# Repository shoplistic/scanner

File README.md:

# Barcode Scanner

### Links
[Headless Setup](https://desertbot.io/blog/headless-pi-zero-w-wifi-setup-windows)  
[Original Source](https://www.pyimagesearch.com/2018/05/21/an-opencv-barcode-and-qr-code-scanner-with-zbar/)

### TODO:
* [x] Install script
* [ ] Diagram / Schematic
* [x] pwm?

### RPi Pinout
|  pin  |  bcm  | usecase         |
| :---: | :---: | :---            |
|  11   |  17   | RED LED         |
|  12   |  18   | LIGHTNING PWM   |
|  13   |  27   | GREEN LED       |
|  15   |  22   | BLUE LED        |
|  16   |  23   | SENSOR          |

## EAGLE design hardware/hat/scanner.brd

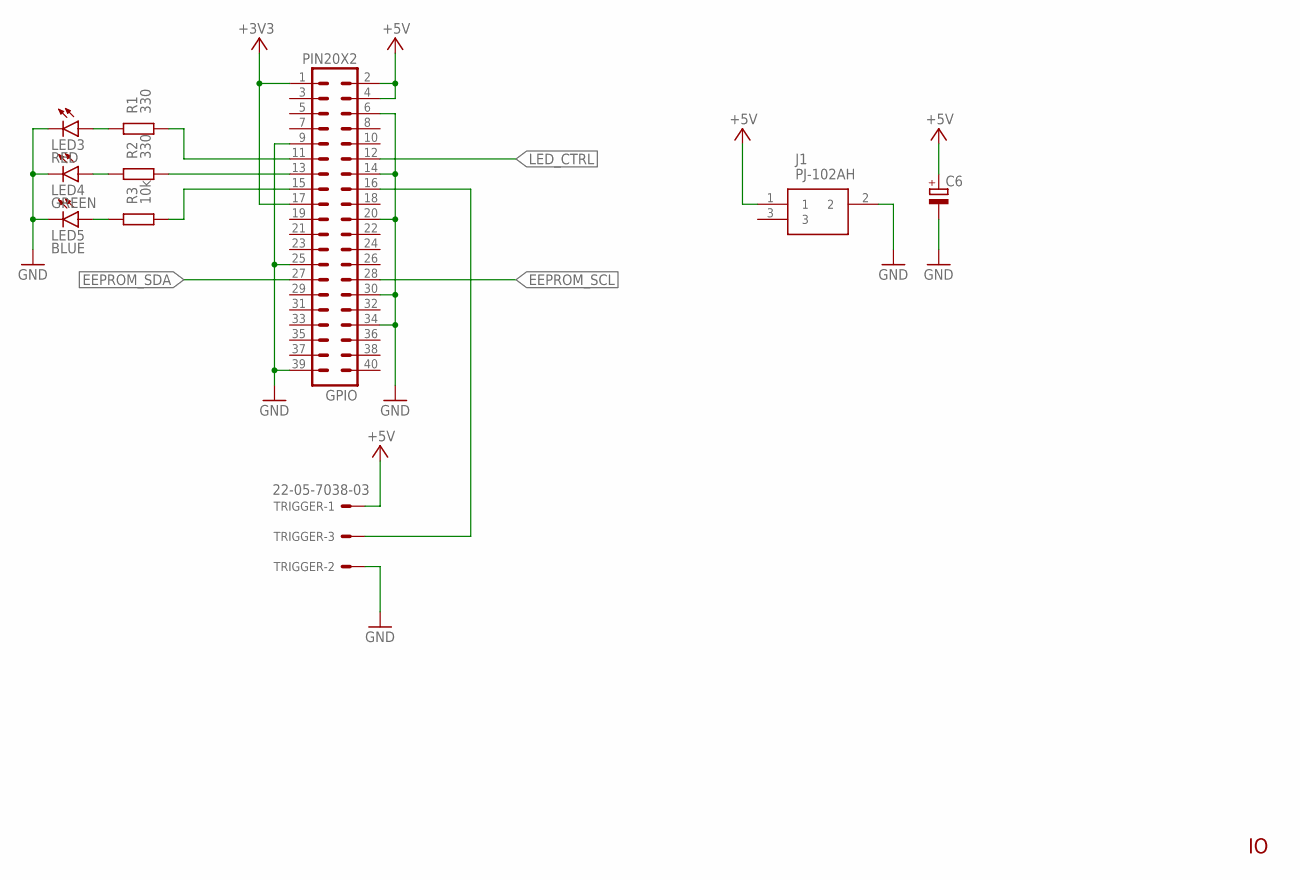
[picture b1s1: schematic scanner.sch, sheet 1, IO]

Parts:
C6: CPOL-EUCT6032; CT6032
GPIO: PIN20X2; PIN_20X2
J1: PJ-102AH
LED3: RED; CHIP-LED0805
LED4: GREEN; CHIP-LED0805
LED5: BLUE; CHIP-LED0805
R1, R2: 330; M0805; TOLERANCE 5%
R3: 10k; M0805; TOLERANCE 5%
TRIGGER: 22-05-7038-03; 7395-03

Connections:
+3V3: GPIO.1, GPIO.17; also elsewhere on the board
+5V: C6.+, GPIO.2, GPIO.4, J1.1, TRIGGER.1; also elsewhere on the board
EEPROM_SCL: GPIO.28; also elsewhere on the board
EEPROM_SDA: GPIO.27; also elsewhere on the board
GND: C6.-, GPIO.6, GPIO.9, GPIO.14, GPIO.20, GPIO.25, GPIO.30, GPIO.34, GPIO.39, J1.2, LED3.C, LED4.C, LED5.C, TRIGGER.2; also elsewhere on the board
LED3: GPIO.11, R1.1
LED4: GPIO.13, R2.1
LED5: GPIO.15, R3.1
LED_CTRL: GPIO.12; also elsewhere on the board
unnamed: LED3.A, R1.2
unnamed: LED4.A, R2.2
unnamed: LED5.A, R3.2
TRIGGER: GPIO.16, TRIGGER.3

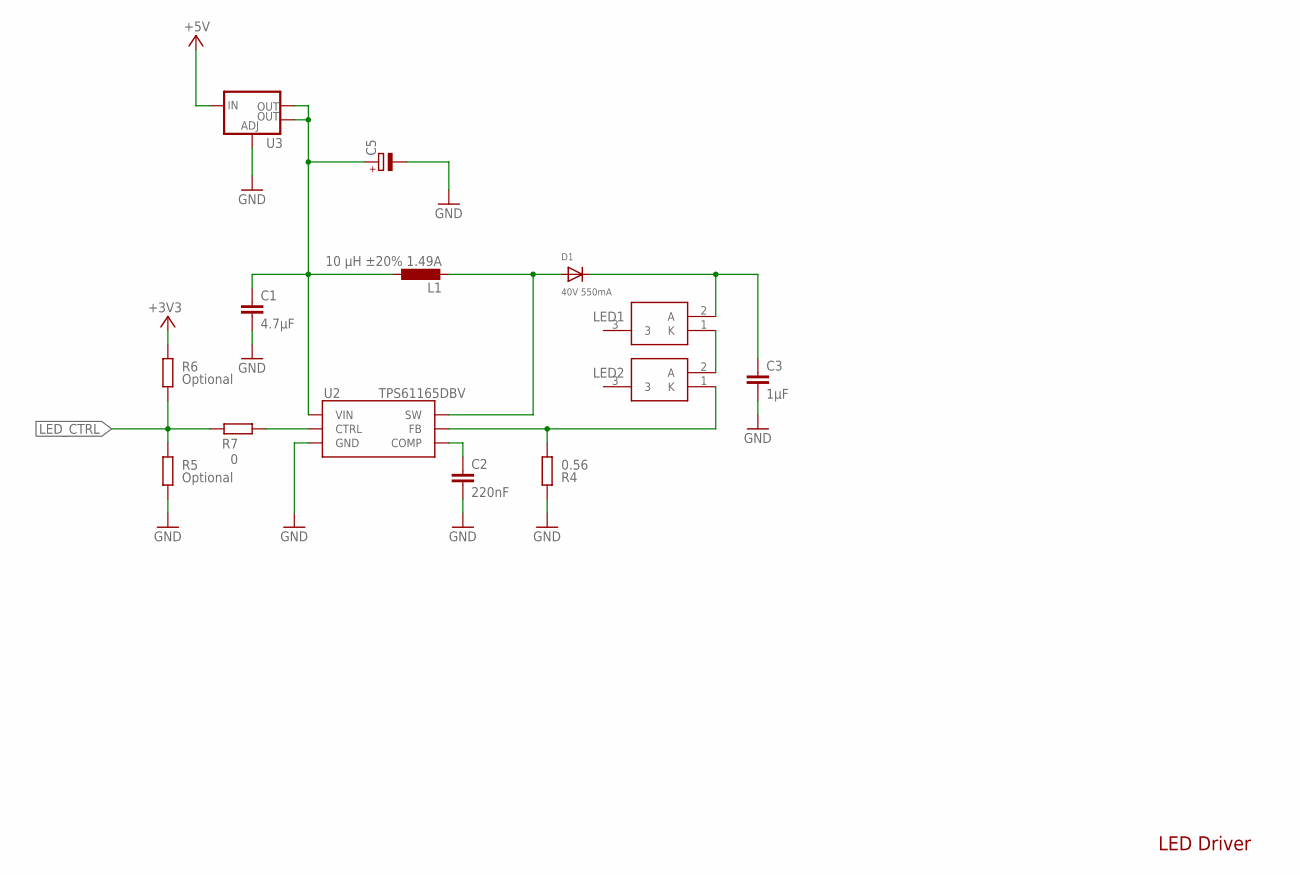
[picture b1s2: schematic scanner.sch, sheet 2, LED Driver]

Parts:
C1: 4.7μF; C0805K
C2: 220nF; C0805K
C3: 1μF; C0805K
C5: CPOL-EUCT6032; CT6032
D1: 40V 550mA; SOD-123
L1: 10 μH ±20% 1.49A; D53LC
LED1, LED2: LW_W5SM-JYKY-JKQL-1; LWW5SMJYKYJKQL1
R4: 0.56; M0805; TOLERANCE 5%
R5, R6: Optional; M0805; TOLERANCE 5%
R7: 0; M0805; TOLERANCE 5%
U2: TPS61165DBV; SOT-23-6
U3: V_REG_LM1117SOT223; SOT223

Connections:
+3V3: R6.2; also elsewhere on the board
+5V: U3.3 (IN); also elsewhere on the board
GND: C1.2, C2.2, C3.2, C5.-, R4.2, R5.1, U2.4 (GND), U3.1 (ADJ); also elsewhere on the board
LED_COMP: C2.1, U2.5 (COMP)
LED_CTRL: R5.2, R6.1, R7.2; also elsewhere on the board
LED_CTRL1: R7.1, U2.2 (CTRL)
LED_FB: LED2.1 (K), R4.1, U2.6 (FB)
LED_SW: D1.A, L1.2, U2.3 (SW)
unnamed: C3.1, D1.C, LED1.2 (A)
unnamed: LED1.1 (K), LED2.2 (A)
VCC: C1.1, C5.+, L1.1, U2.1 (VIN), U3.2 (OUT), U3.4 (OUT)

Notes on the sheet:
LED Driver

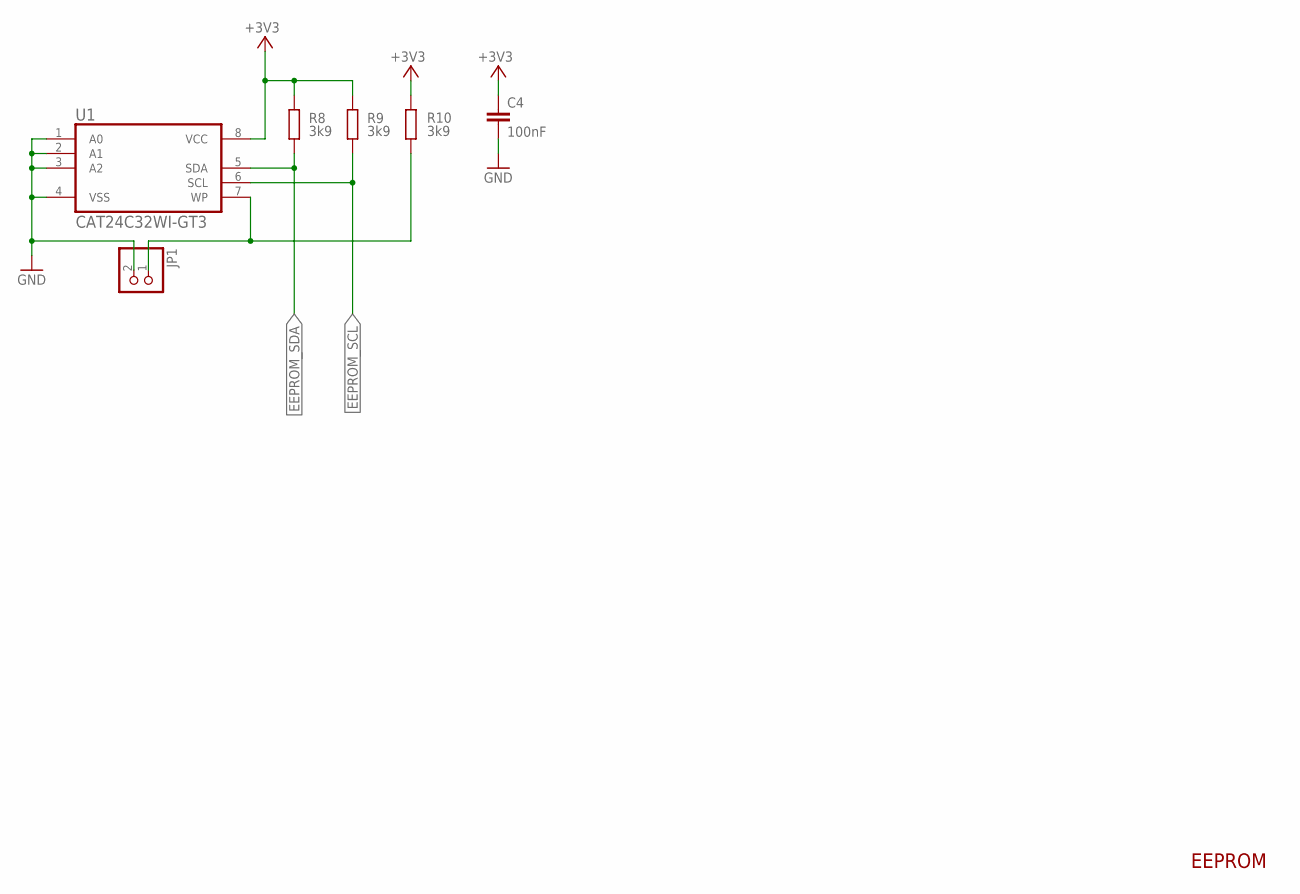
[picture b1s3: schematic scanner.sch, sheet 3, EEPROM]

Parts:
C4: 100nF; C0805K
JP1: PINHD-1X2; 1X02
R8, R9, R10: 3k9; M0805; TOLERANCE 5%
U1: CAT24C32WI-GT3; SOIC127P600X175-8N

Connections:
+3V3: C4.1, R8.2, R9.2, R10.1, U1.8 (VCC); also elsewhere on the board
EEPROM_SCL: R9.1, U1.6 (SCL); also elsewhere on the board
EEPROM_SDA: R8.1, U1.5 (SDA); also elsewhere on the board
EEPROM_WP: JP1.1, R10.2, U1.7 (WP)
GND: C4.2, JP1.2, U1.1 (A0), U1.2 (A1), U1.3 (A2), U1.4 (VSS); also elsewhere on the board

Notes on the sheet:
EEPROM

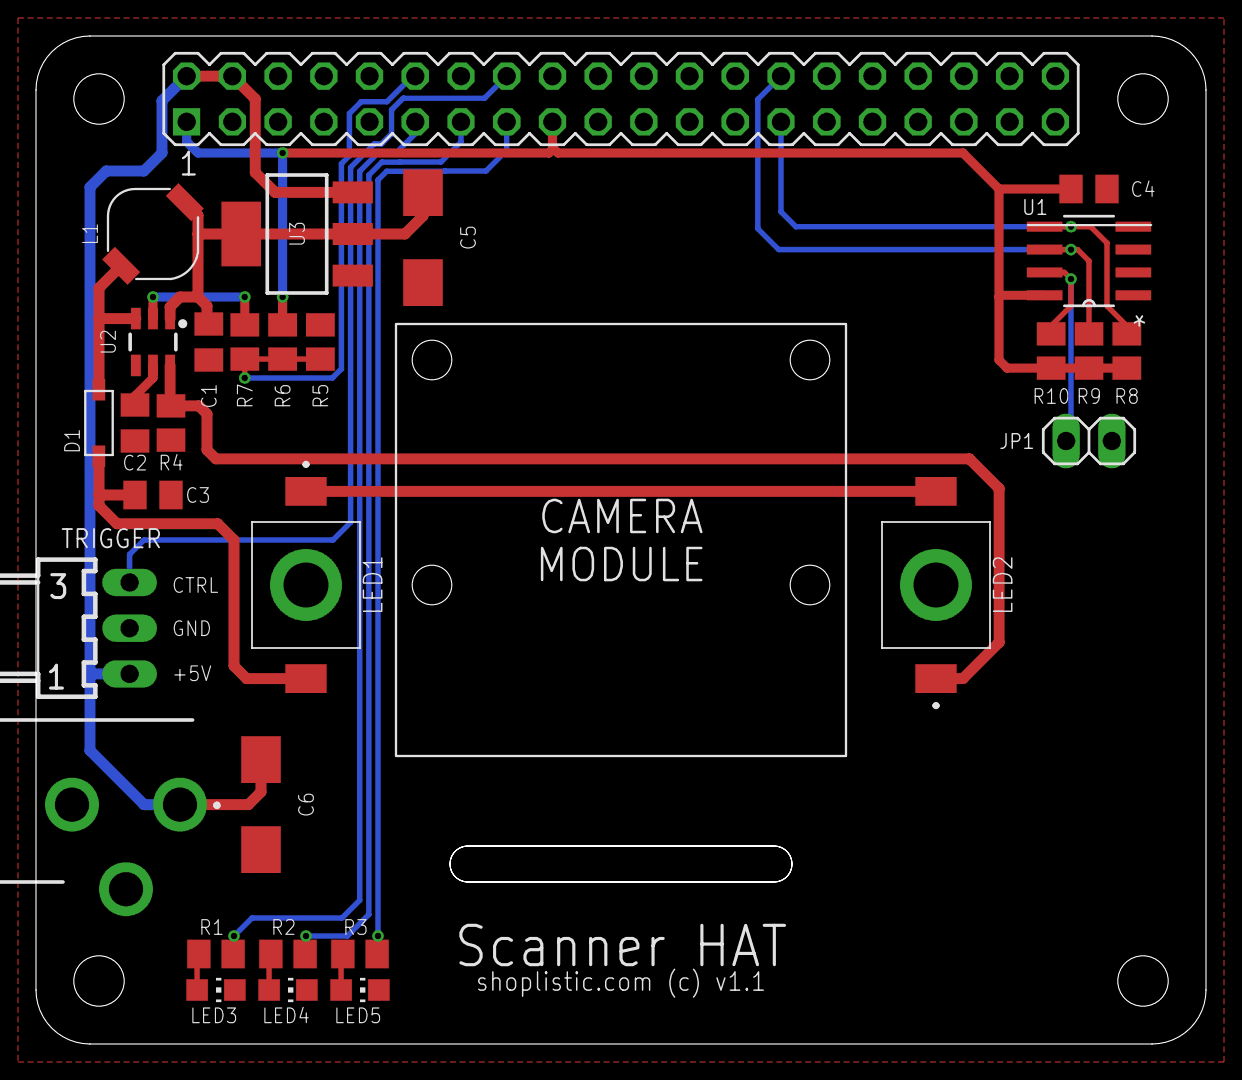
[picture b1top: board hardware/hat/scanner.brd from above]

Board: 2 copper layers, 65.0 x 56.0 mm, 30 parts (0 on the bottom side), 21 nets.

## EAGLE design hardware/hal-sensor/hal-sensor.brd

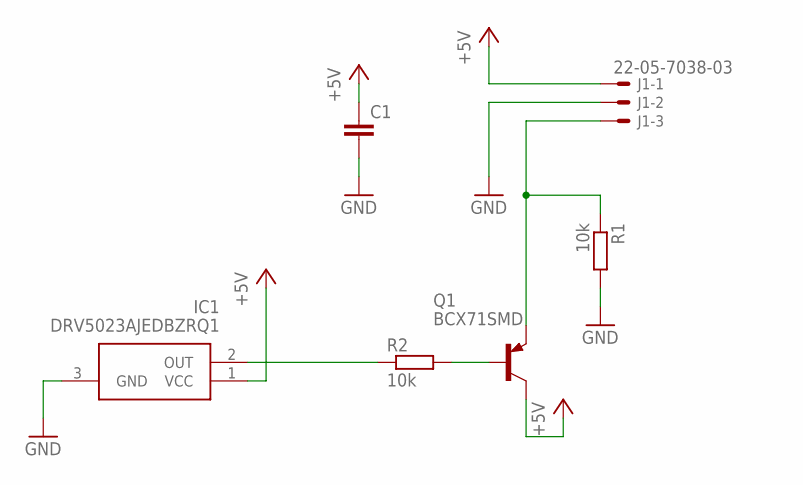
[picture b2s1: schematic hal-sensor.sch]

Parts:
C1: C-EUC0805; C0805
IC1: DRV5023AJEDBZRQ1; SOT95P237X112-3N
J1: 22-05-7038-03; 7395-03
Q1: BCX71SMD; SOT23
R1, R2: 10k; R0805

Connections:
+5V: C1.1, IC1.1 (VCC), J1.1, Q1.3 (C)
CTRL: J1.3, Q1.2 (E), R1.1
GND: C1.2, IC1.3 (GND), J1.2, R1.2
unnamed: IC1.2 (OUT), R2.1
unnamed: Q1.1 (B), R2.2

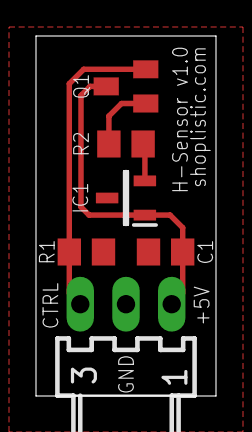
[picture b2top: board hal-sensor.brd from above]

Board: 2 copper layers, 10.0 x 20.0 mm, 6 parts (0 on the bottom side), 5 nets.

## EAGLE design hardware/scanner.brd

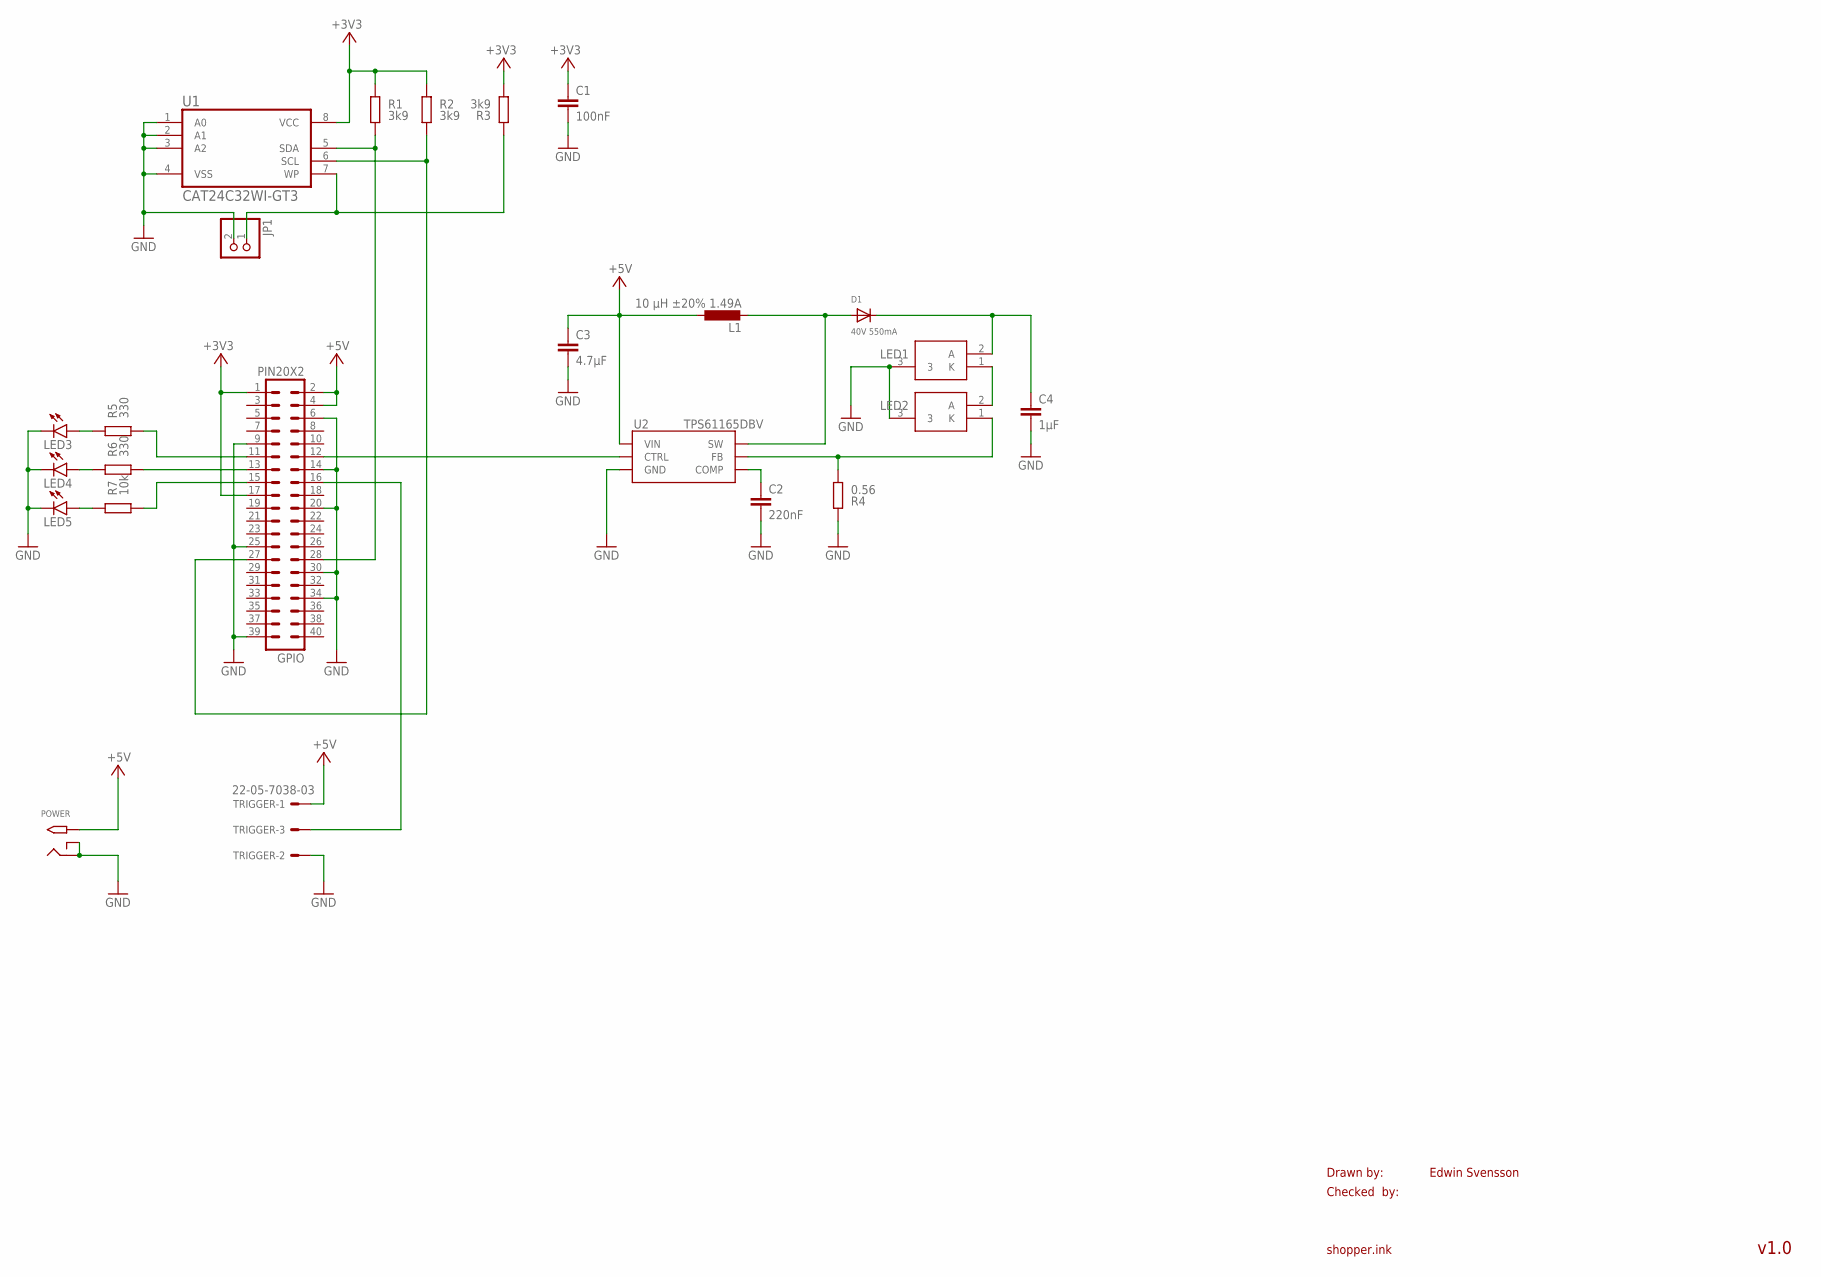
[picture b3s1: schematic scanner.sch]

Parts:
C1: 100nF; C0805K
C2: 220nF; C0805K
C3: 4.7μF; C0805K
C4: 1μF; C0805K
D1: 40V 550mA; SOD-123
GPIO: PIN20X2; PIN_20X2
JP1: PINHD-1X2; 1X02
L1: 10 μH ±20% 1.49A; D53LC
LED1, LED2: LW_W5SM-JYKY-JKQL-1; LWW5SMJYKYJKQL1
LED3, LED4, LED5: LEDCHIP-LED0805; CHIP-LED0805
POWER: 2.1MMJACKTHM; PJ-102A
R1, R2, R3: 3k9; M0805; TOLERANCE 5%
R4: 0.56; M0805; TOLERANCE 5%
R5, R6: 330; M0805; TOLERANCE 5%
R7: 10k; M0805; TOLERANCE 5%
TRIGGER: 22-05-7038-03; 7395-03
U1: CAT24C32WI-GT3; SOIC127P600X175-8N
U2: TPS61165DBV; SOT-23-6

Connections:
+3V3: C1.1, GPIO.1, GPIO.17, R1.2, R2.2, R3.1, U1.8 (VCC)
+5V: C3.1, GPIO.2, GPIO.4, L1.1, POWER.TIP, TRIGGER.1, U2.1 (VIN)
EEPROM_SCL: GPIO.27, R2.1, U1.6 (SCL)
EEPROM_SDA: GPIO.28, R1.1, U1.5 (SDA)
EEPROM_WP: JP1.1, R3.2, U1.7 (WP)
GND: C1.2, C2.2, C3.2, C4.2, GPIO.6, GPIO.9, GPIO.14, GPIO.20, GPIO.25, GPIO.30, GPIO.34, GPIO.39, JP1.2, LED1.3, LED2.3, LED3.C, LED4.C, LED5.C, POWER.RING, POWER.RING_SW, R4.2, TRIGGER.2, U1.1 (A0), U1.2 (A1), U1.3 (A2), U1.4 (VSS), U2.4 (GND)
LED3: GPIO.11, R5.1
LED4: GPIO.13, R6.1
LED5: GPIO.15, R7.1
LED_CTRL: GPIO.12, U2.2 (CTRL)
LED_FB: LED2.1 (K), R4.1, U2.6 (FB)
LED_SW: D1.A, L1.2, U2.3 (SW)
unnamed: C2.1, U2.5 (COMP)
unnamed: C4.1, D1.C, LED1.2 (A)
unnamed: LED1.1 (K), LED2.2 (A)
unnamed: LED3.A, R5.2
unnamed: LED4.A, R6.2
unnamed: LED5.A, R7.2
TRIGGER: GPIO.16, TRIGGER.3

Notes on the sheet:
Drawn by:
Checked by:
shopper.ink
Edwin Svensson
v1.0

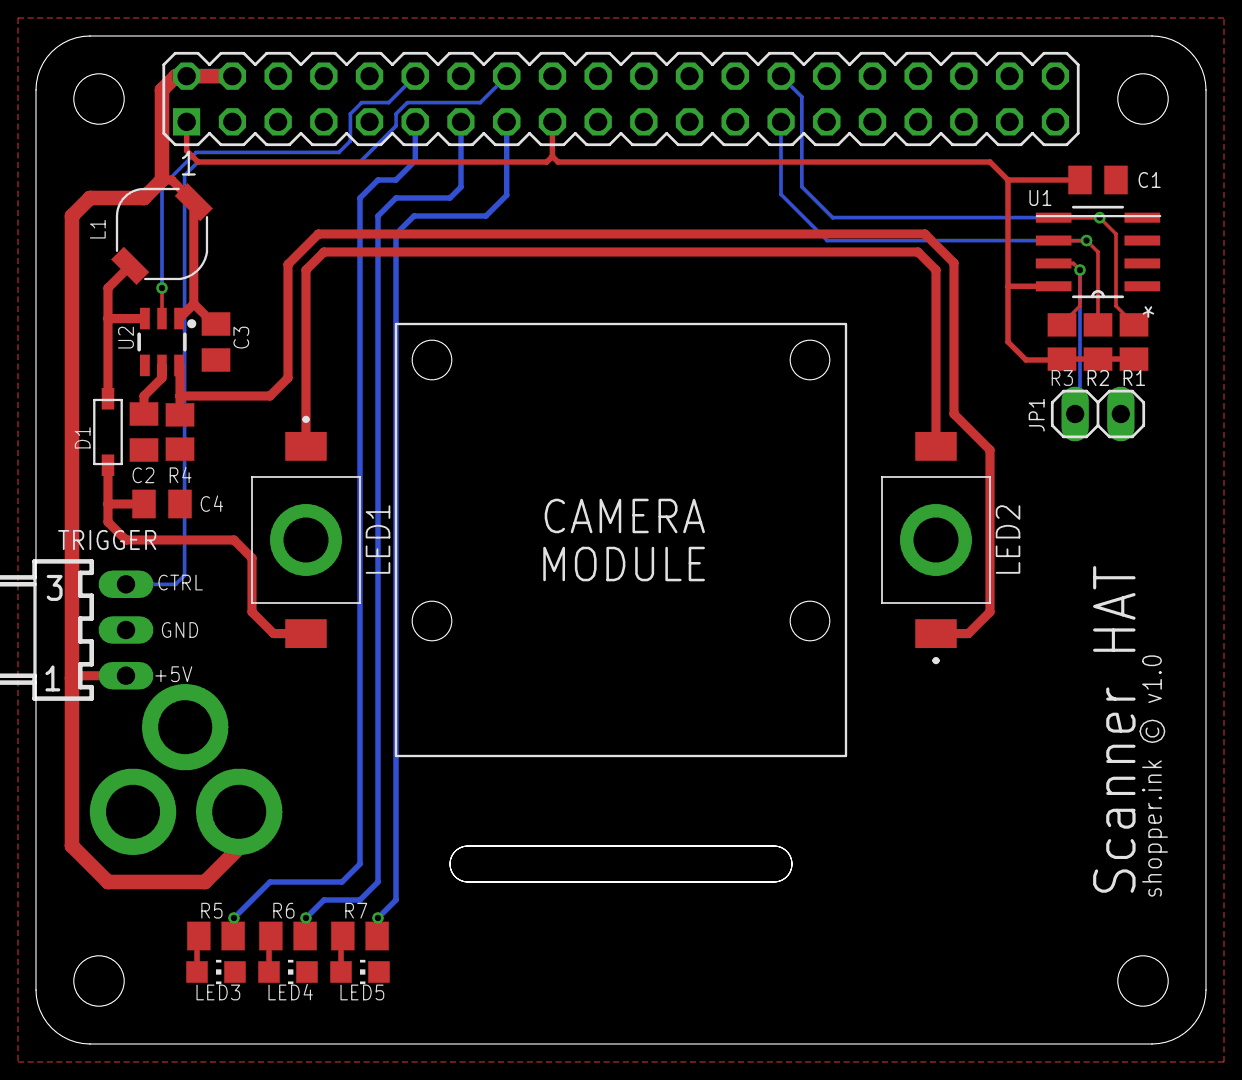
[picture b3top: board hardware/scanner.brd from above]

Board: 2 copper layers, 65.0 x 56.0 mm, 24 parts (1 on the bottom side), 19 nets.

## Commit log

2018-10-27 rpizw pinout
2018-10-27 moved things
2018-10-27 added Pi2c
2018-10-27 makefile
2018-10-28 i2c read / write
2018-10-28 Updated main.cpp
2018-10-28 move things arround, namespace
2018-10-28 re-add Pi2c submodule
2018-10-29 show debug window
2018-11-19 add api and iri2c
2018-11-20 add leds
2018-11-20 install script
2018-12-02 tps61165 version
2018-12-02 added pinout
2018-12-04 add hat files
2018-12-04 update hat
2018-12-04 move eagle libs
2018-12-05 add libs
2018-12-05 update pcb
2018-12-06 added camera mounting holes
2018-12-07 update bom
2018-12-07 update board layout
2018-12-11 new power connector
2018-12-11 rename routes
2018-12-12 update text
2018-12-12 switch > sensor
2018-12-12 added proper sensor connector
2018-12-15 revert to require low signal
2018-12-15 update board
2018-12-15 exclude ods swap
2018-12-15 final layout?
2018-12-15 address drc complaints, fixed font
2018-12-19 redo eeprom area
2018-12-21 move to hat/
2018-12-22 add library
2018-12-22 add HALL sensor board
2018-12-22 make vias symetrical
2018-12-22 move label
2018-12-28 fixed issues with 1.0
2018-12-28 added PJ-102AH lib
2018-12-28 change pin to 23
2018-12-28 add labels
2018-12-28 add 3V3 regulator
2018-12-29 remove eagle lib
2018-12-29 v1.1-d1
2018-12-29 update url
2018-12-29 Create LICENSE
2019-01-02 update layout
2019-01-02 tweak layout
2019-01-03 redo hall sensor board
2019-01-03 tweak hal sensor board
2019-01-03 remove gerber files
2019-01-03 update api url
2019-01-03 v.1.1-final
2019-01-11 change dc to 1%
2019-01-12 added systemd service
2019-08-08 add packages
2019-08-08 reduce fs activity
2019-08-08 move to hardware

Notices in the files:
hardware/scanner.brd:
shopper.ink © v1.0
parts and their libraries:
m-pad-2.1: License : GNU General Public License version 2 (see bottom)
SparkFun-IC-Power: Licensing: Creative Commons ShareAlike 4.0 International - https://creativecommons.org/licenses/by-sa/4.0
